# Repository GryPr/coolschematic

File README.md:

# KiBot CI/CD template repository for KiCad 5

123

This repository provides a ready-to-go CI/CD workflow for KiCad 5 with GitHub actions.

## Features of this repository template

1. Integration with GitHub releases to automatically produce documentation and
   fabrication files on every GitHub release, including automatic date and version
   stamping of schematics and PCBs.
2. KiBot preflighting on every pull request (ERC/DRC checks disabled by default).
3. VSCode dev container and default build task for easy local testing of KiBot scripts.

## Creating your GitHub repo and KiCad project

To create a KiCad project using this GitHub template:

1. Hit the _Use this template_ button then follow the steps from GitHub to create a copy of the repo. **The repository name must exactly match the name of the KiCad project.
   Do not use spaces in either the repository or the project name.**
2. Clone the new repo locally.
3. Go to _File_ > _New_ > _Project..._ in KiCad.
4. Name the project the exact same name as the GitHub repository name.
5. Uncheck the _Create a new directory for this project_ option. **This is very important!**
6. Save the project into the top level of the folder for the GitHub repository.

Do not use spaces in the GitHub repository or KiCad project name. Use underscores or hyphens instead, for example `TBM930_De-Ice_-_Panel` or `Collins-FMS-3000`.

If you've done all the steps correctly the folder structure will look similar like this:

Notice that the folder name (which is also the GitHub repo name) and project name are exactly the same and there are no spaces.

## Setting up date and version number replacement

The GitHub automation can automatically set the date and version number in the generated schematic and PCBs. Before using this make sure
to set the timezone to your local timezone in the `.github\workflows\documentation-only.yml` and `.github\workflows\release.yml` files.

Version number and date replacement is done on the `%%version%%` and `%%date%%` string wherever they appear in your `.sch` and `.kicad_pcb` files.
Typically you will use them in the _Page settings_ dialog for the schematic and as text in silkscreen and/or copper layers on your board:

## Documentation generated

The following documents are generated on every release build:

- Interactive BOM - HTML
- Schematic - PDF
- PCB front copper and explanatory drawings layers - PDF
- PCB back copper and explanatory drawings layers - PDF
- 3D render - STEP
- PCB front - JPEG
- PCB back - JPEG

These documents can also be generated by manually running the `KiBot - Generate documentation` action on GitHub.

## Fabrication files generated

The following fabrication files are generated on every release build:

- JLCPCB gerbers and drill files, with BOM and placement files for SMT service
- PCBWay gerbers and drill files

The fabrication files can also be generated by manually running the `KiBot - Release` action on GitHub.

## How this works

A complete CodeTour is included in this repository that walks through all the components
of how KiBot scripts and GitHub actions work. [Use github.dev to view the CodeTour](https://github.dev/neilenns/KiBot-CICD-Template)!

## Running builds locally

This repository template includes the files necessary to run in a VSCode dev container,
which dramatically reduces the effort required to use KiBot on Windows machines.

Never used VSCode remote containers before on Windows? Here's how to get set up:

1. From a PowerShell install WSL2 with this command: `wsl --install`
2. Install [Visual Studio Code](https://code.visualstudio.com/Download) and Docker Desktop(https://www.docker.com/products/docker-desktop)
3. Install the [Remote Containers](https://marketplace.visualstudio.com/items?itemName=ms-vscode-remote.remote-containers) extension for VSCode

When installing Docker Desktop you may be told you have to enable virtualization in your computer's BIOS. Setting that up
is outside the scope of this readme but isn't hard. Just do a web search for your motherboard for how to enter the BIOS
and what the exact name of the setting is, then turn it on.

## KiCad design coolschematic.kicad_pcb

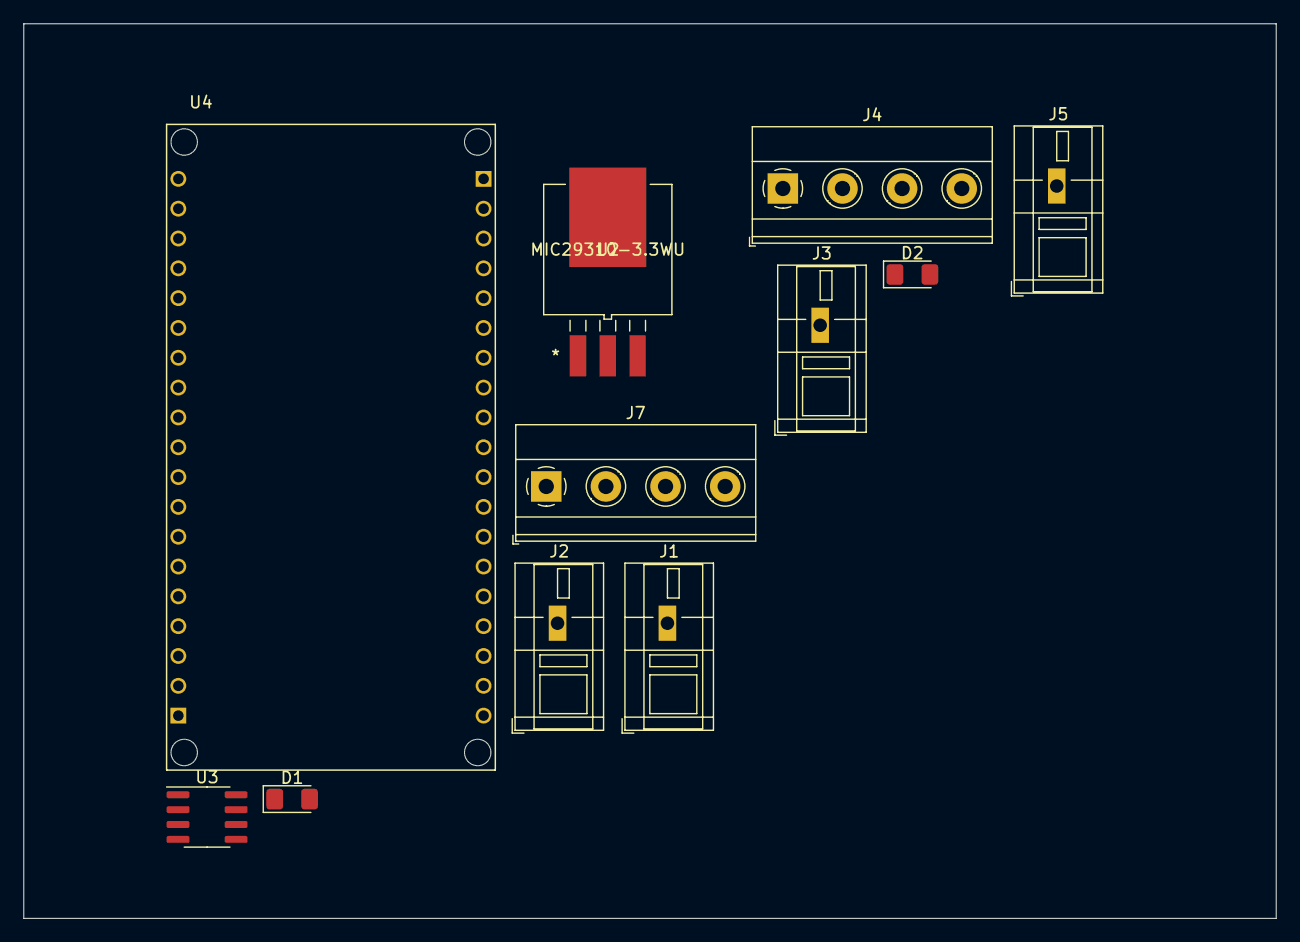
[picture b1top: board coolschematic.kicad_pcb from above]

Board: 2 copper layers, 106.7 x 76.2 mm, 11 parts (0 on the bottom side), 20 nets, no tracks yet.

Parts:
D1: MLEGRN-A1-0000-000X01; LED_1206_3216Metric_Pad1.42x1.75mm_HandSolder
D2: MLBAWT-A1-0000-000W51; LED_1206_3216Metric_Pad1.42x1.75mm_HandSolder
J1, J2, J3, J5: 1706730; TerminalBlock_WAGO_236-101_1x01_P5.00mm_45Degree
J4, J7: 1935187; TerminalBlock_Phoenix_MKDS-1,5-4-5.08_1x04_P5.08mm_Horizont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
U2: MIC29310-3.3WU
U3: INA219AxD; SOIC-8_3.9x4.9mm_P1.27mm
U4: ESP32_NODEMCU; MODULE_ESP32_NODEMCU

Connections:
+3.3V: U2.3 (OUT), U3.5 (VS), U4.J5_18 (EN), U4.J5_19 (3V3)
/DIR: U4.J4_5 (RXD), U4.J5_11 (G25)
/MODE0: U4.J5_8 (G14), U4.J5_12 (G33)
/MODE1: U4.J4_16 (G15), U4.J5_13 (G32)
/MODE2: U4.J4_9 (G18), U4.J5_9 (G27)
/STEP: U4.J4_8 (G19), U4.J5_10 (G26)
/nENBL: U4.J4_2 (G23), U4.J4_4 (TXD)
/nRESET: U4.J4_3 (G22), U4.J4_11 (G17)
/nSLEEP: U4.J4_6 (G21), U4.J4_12 (G16)
GND: U2.2 (GND), U4.J5_6 (GND)
unnamed: D1.2 (A), U4.J5_5 (G13)
unnamed: D2.2 (A), U4.J5_7 (G12)
unnamed: J1.1, U2.1 (IN)
unnamed: J2.1, U3.8 (IN+)
unnamed: J3.1, U3.7 (IN-)
unnamed: J5.1, U3.6 (GND)
unnamed: U3.1 (A1), U4.J4_13 (G4)
unnamed: U3.2 (A0), U4.J4_10 (G5)
unnamed: U3.3 (SDA), U4.J4_14 (G0)
unnamed: U3.4 (SCL), U4.J4_15 (G2)

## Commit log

2022-12-21 Change schematic location
2022-12-21 Fix naming
2022-12-21 Fix on push inputs
2022-12-21 Change kibot version
2022-12-21 Change to kicad 6
2022-12-21 Update PCB
2022-12-21 Test
2022-12-21 Test2
2022-12-21 Test3

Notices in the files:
parts and their libraries:
Copyright 2021 Accelerated Designs. All rights reserved.
